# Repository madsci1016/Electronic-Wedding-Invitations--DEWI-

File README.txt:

/*
 * WeddingCard.c
 *
 * Created: 11/13/2012 8:11:05 PM
 *  Author: Bill&Mara
 *
 *	For project details see: http://www.billporter.info/?p=1655
 *
 *		 

*This program is free software: you can redistribute it and/or modify it under the terms of the GNU General Public License as published by the Free Software Foundation, either version 3 of the License, or(at your option) any later version.
This program is distributed in the hope that it will be useful,
but WITHOUT ANY WARRANTY; without even the implied warranty of
MERCHANTABILITY or FITNESS FOR A PARTICULAR PURPOSE.  See the
GNU General Public License for more details.
<http://www.gnu.org/licenses/>
*
*This work is licensed under the Creative Commons Attribution-ShareAlike 3.0 Unported License. 
*To view a copy of this license, visit http://creativecommons.org/licenses/by-sa/3.0/ or
*send a letter to Creative Commons, 444 Castro Street, Suite 900, Mountain View, California, 94041, USA.

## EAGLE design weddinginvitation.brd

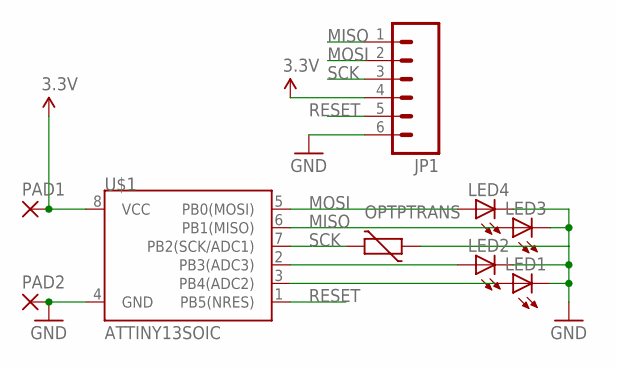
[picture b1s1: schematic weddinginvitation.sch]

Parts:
JP1: M06SMD-FEMALE-V2; 1X06-SMD-FEMALE-V2
LED1, LED2, LED3, LED4: LED1206; LED-1206
OPTPTRANS: VARISTORCN0805; CT/CN0805
PAD1, PAD2: SMD5; SMD2,54-5,08
U$1: ATTINY13SOIC; SO08

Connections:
3.3V: JP1.4, PAD1.1, U$1.8 (VCC)
GND: JP1.6, LED1.C, LED2.C, LED3.C, LED4.C, OPTPTRANS.1, PAD2.1, U$1.4 (GND)
MISO: JP1.1, LED3.A, U$1.6 (PB1(MISO))
MOSI: JP1.2, LED4.A, U$1.5 (PB0(MOSI))
unnamed: LED1.A, U$1.3 (PB4(ADC2))
unnamed: LED2.A, U$1.2 (PB3(ADC3))
RESET: JP1.5, U$1.1 (PB5(NRES))
SCK: JP1.3, OPTPTRANS.2, U$1.7 (PB2(SCK/ADC1))

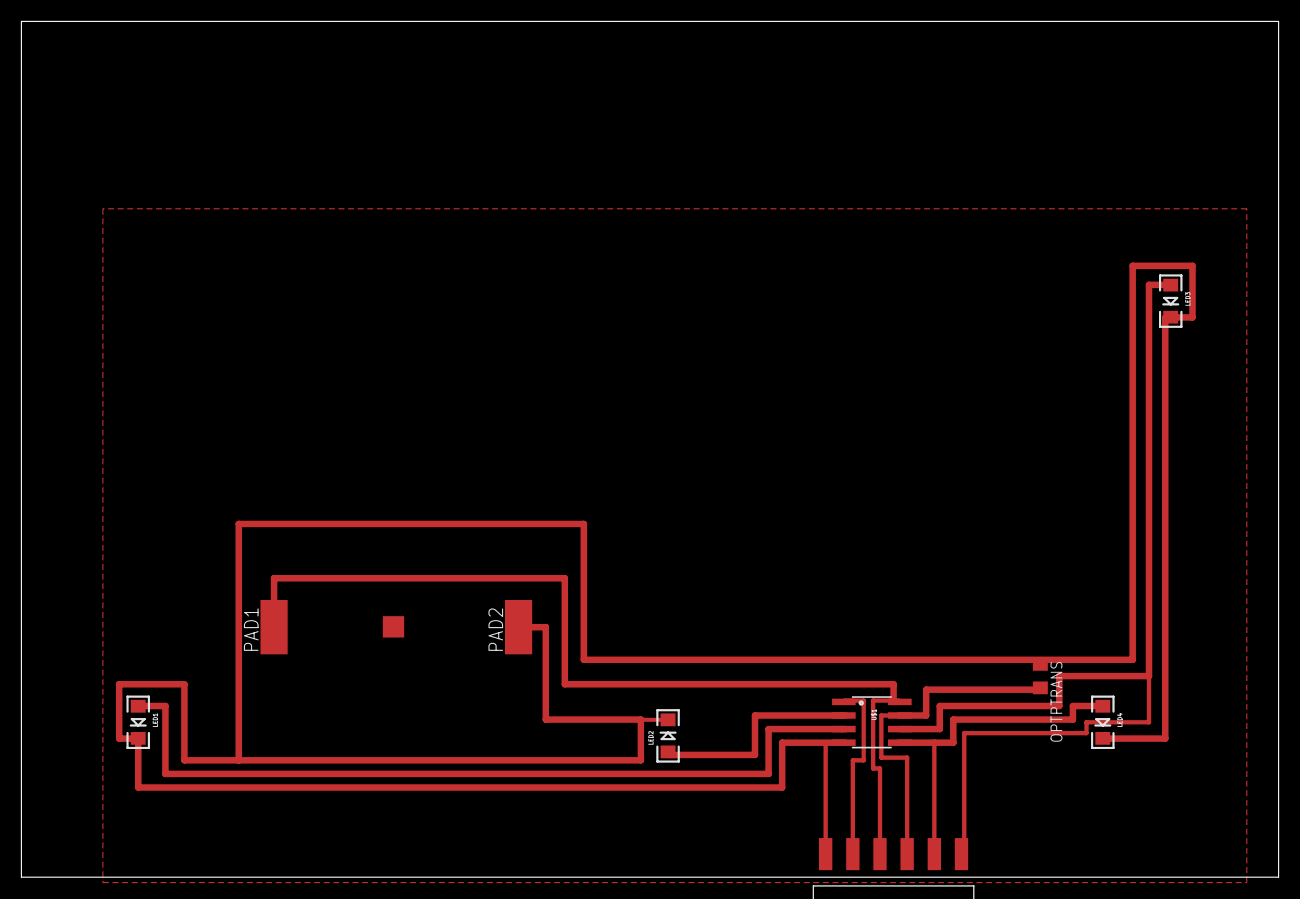
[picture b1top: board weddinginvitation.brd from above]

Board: 2 copper layers, 117.5 x 80.0 mm, 9 parts (0 on the bottom side), 8 nets.

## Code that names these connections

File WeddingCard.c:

/*
 * WeddingCard.c
 *
 * Created: 11/13/2012 8:11:05 PM
 *  Author: Bill&Mara
 *
 *	For project details see: http://www.billporter.info/?p=1655
 *
 *		Theory for sleep and light sensing inspired by:
 *			http://spritesmods.com/?art=minimalism&page=4	
 *				Though there were some bugs in the code and it didn't follow AVR Clib instructions
 *				for safe sleep; so I mostly rewrote the code to correct. 

 *
 */ 




#define F_CPU 1200000UL  // 1.2 MHz Though really it is less than this. timings will be off; not important

#include <util/delay.h>
#include <avr/io.h>
#include <avr/interrupt.h>
#include <avr/pgmspace.h>
#include <avr/sleep.h>
#include <avr/wdt.h>

//LED names match schematic. Backwards, I know. 
#define LED1 PB4 //ADC 2
#define LED2 PB3 //ADC 3
#define LED3 PB1 
#define LED4 PB0
#define SENSOR PB2 //ADC 1




//these ASM macros configure the WatchDog timer for interrupt only mode without touching the reset bit. 
//using the AVRClib macros (which touch the reset bit) was causing unexpected behavior. 
//pulled from http://www.avrfreaks.net/index.php?name=PNphpBB2&file=printview&t=51070&start=0
//It also means we don't need to keep touching the WDT interrupt bit.

#define wdt_set(value)   \
    __asm__ __volatile__ (  \
        "in __tmp_reg__,__SREG__" "\n\t"    \
        "cli" "\n\t"    \
        "wdr" "\n\t"    \
        "sts %0,%1" "\n\t"  \
        "out __SREG__,__tmp_reg__" "\n\t"   \
        "sts %0,%2" \
        : /* no outputs */  \
        : "M" (_SFR_MEM_ADDR(_WD_CONTROL_REG)), \
        "r" (_BV(_WD_CHANGE_BIT) | _BV(WDE)), \
            "r" ((uint8_t) ((value & 0x08 ? _WD_PS3_MASK : 0x00) | \
                _BV(WDTIE) | (value & 0x07)) ) \
        : "r0"  \
    ) 


#define wdt_off(x)   \
    __asm__ __volatile__ (  \
        "in __tmp_reg__,__SREG__" "\n\t"    \
        "cli" "\n\t"    \
        "wdr" "\n\t"    \
        "sts %0,%1" "\n\t"  \
        "sts %0,%2" \
        : /* no outputs */  \
        : "M" (_SFR_MEM_ADDR(_WD_CONTROL_REG)), \
        "r" (_BV(_WD_CHANGE_BIT) | _BV(WDE)), \
            "r" ((uint8_t) (0x00)) \
        : "r0"  \
    ) 

#define SETLOW(pin) (PORTB&=~(1<<pin))
#define ALLLEDS (1<<LED1)|(1<<LED2)|(1<<LED3)|(1<<LED4)

uint8_t incrementFrame(uint8_t);
void lightShow(void);
uint16_t getLight(void);
void easterEgg(void);
void powerOffUc(void);

//sparkle effect PWM values generated by Vixen Light Show software
static PROGMEM prog_uint8_t vixen_show_data[] = {0,0,0,178,163,148,133,118,103,88,73,58,43,0,0,0,0,0,178,163,148,178,178,163,148,133,118,178,163,178,163,148,133,118,103,178,178,163,148,133,118,178,163,148,178,178,163,148,133,178,163,148,133,118,178,163,148,178,163,178,178,163,148,133,178,178,163,148,178,163,148,133,178,163,148,133,178,178,163,148,133,178,163,148,178,163,178,163,148,133,118,103,178,163,148,178,178,163,148,178,163,148,133,118,103,178,163,148,178,178,163,148,133,118,103,88,73,58,43,178,163,148,133,118,103,88,73,58,43,0,0,0,0,0,0,0,0,0,0,0,0,0,178,163,178,163,148,133,178,178,163,148,133,118,103,88,178,163,148,133,118,103,178,163,148,133,118,103,88,73,58,43,0,0,178,163,178,163,148,133,118,103,88,73,58,178,163,148,133,118,103,88,73,58,43,0,178,127,76,0};

//easter egg storage
static PROGMEM prog_uint8_t easteregg[]={"-... .. .-.. .-.. / .- -. -.. / -- .- .-. .- / --. . . -.- ... / - --- --. . - .... . .-. / ..-. --- .-. . ...- . .-. .-.-.-"};
	
uint8_t frame1, frame2, frame3, frame4; //index for each LED channel
uint8_t match1, match2, match3, match4; //match compare for Software PWM
uint8_t triggercount;

uint16_t threshold;

int main(void)
{
	
	//set IO Direction
	DDRB = ALLLEDS;	
	
	//flash all LEDs on/off
	PORTB = ALLLEDS;
	_delay_ms(200);
	PORTB = 0;
	_delay_ms(1000);
	
	//From here on in the micro will always be powered. So we'll capture ambient light first and store it as the threshold. 
	//this means shorting reset will re-cal this threshold
	threshold = getLight();
	//egthreshold = getLight(ALED2);
	
	//flash all LEDs on/off
	PORTB = ALLLEDS;
	_delay_ms(200);
	PORTB = 0;
	//_delay_ms(1000);
	
	
	//lets go ahead and get ready for bed
	set_sleep_mode(SLEEP_MODE_PWR_DOWN);
	
	//main 'loop'
	while(1){
		//see if we should go to sleep or start the show
		if(getLight()<threshold) 						
			lightShow();
		else
			powerOffUc();
			

	}
	
    
}	

uint16_t getLight(void) {
    
	uint16_t val;
    
	
	//select correct ADC pin and voltage reference
	ADMUX=(1<<REFS0)|(1<<MUX0);
    ADCSRA=0x83;//enable adc, max prescaler
	
	//turn on pullup
	PORTB = (1<<SENSOR);
	
	//read ADC
    ADCSRA|=0x40; //go do adc
    while(ADCSRA&0x40) ; //wait till adc is done
    val=ADC;
	
	//disable adc
    ADCSRA=0; 
	
	//turn off pullup
    PORTB = 0;
	
    return val;
}


void lightShow(void){
	
	//make sure they are set to output
    DDRB = ALLLEDS;
	
	//load index starts
	frame1=0;
	frame2=50;
	frame3=100;
	frame4=150;
	
	for(uint8_t z=0; z<=200; z++)//run the show for 20 seconds. 
		{
			//Software PWM for the 4 channels. 
		
			//load match compares from program memory. Doing this once each time saves cycles.
			match1 = pgm_read_byte(&(vixen_show_data[frame1]));
			match2 = pgm_read_byte(&(vixen_show_data[frame2]));
			match3 = pgm_read_byte(&(vixen_show_data[frame3]));
			match4 = pgm_read_byte(&(vixen_show_data[frame4]));
		
			//freerun PWM for so many times and set pin low on compare
			for(uint8_t y=0; y<18; y++){ //each y is a PWM period. run so many PWM periods. See clock math below
				
				//set all pins HIGH
				PORTB = ALLLEDS;
				
				for(uint8_t i=0; i<255; i++){ //each i is a PWM division where compares should be made
					if(match1 == i) SETLOW(LED1); //each of these lines take 4 clocks 
					if(match2 == i) SETLOW(LED2);
					if(match3 == i) SETLOW(LED3);
					if(match4 == i) SETLOW(LED4); //so I used 16 clocks to compare all channels. 
					
					//16 clocks per PWM division x 255 divisions = 4080 clocks per PWM period
					//at 1.2Mhz that's a PWM freq of ~300 Hz. Good enough, no need to delay
					//Since Light show is 10Hz, each PWM period should be repeated 30 times. 
					// But with 3V the RC oscillator runs slower than predicted. Changed to 
					// 18 times through experimentation. 
				}
				
			
			}
		
		//move frame index's up
		frame1 = incrementFrame(frame1);
		frame2 = incrementFrame(frame2);
		frame3 = incrementFrame(frame3);
		frame4 = incrementFrame(frame4);
	}
	
		//after show, run easter egg if led is in dark
	if(getLight()>threshold) 
		easterEgg();
}

//quick function to move indexs up by one and wrap around
uint8_t incrementFrame(uint8_t framez) {
	
	framez++;
	if (framez > 199) framez = 0;
	
	return framez;
}

void easterEgg(){
	
	//make sure they are set to output
    //DDRB = 0b00011110;
	
	#define timeunit 180
	
	_delay_ms(timeunit*7);
	
	char temp = 0;
	
	for(int i=0; i<sizeof(easteregg); i++){
		
		temp = pgm_read_byte(&(easteregg[i]));
		
		if (temp == '.') {
			//set all pins HIGH
			PORTB = ALLLEDS;
			_delay_ms(timeunit);
			PORTB = 0;
			_delay_ms(timeunit);
		}
		else if (temp == '-') {
			//set all pins HIGH
			PORTB = ALLLEDS;
			_delay_ms(timeunit*3);
			PORTB = 0;
			_delay_ms(timeunit);
		}
		else if (temp == ' ') {
			//interletter delay, 3 dots
			_delay_ms(timeunit*3);
		}
		else //interword delay, 7 dots
			_delay_ms(timeunit*7);
		
	}
	
}

ISR(WDT_vect) {
		//empty interrupt routine 

}

//Configure the uC for power saving and enter sleep
//As written this function will return when the Watchdog alarm goes off.
//but won't reset the uC so RAM is safe. 
void powerOffUc(void) {
    
	//set IO for power save
	PORTB=0; DDRB=0;
	//get ready for bed
	sleep_enable();
	//need interrupts running for WDT alarm to work
	sei();
	//set wakeup for 2 seconds from now
	wdt_set(WDTO_2S);
	//go to sleep
	sleep_cpu();
	//wake up from sleep
	sleep_disable();  
	//turn off alarm
	wdt_off(); 
	//I don't use interrupts anyway. Leave em off. 
	cli();
}

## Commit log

2013-01-30 Added Eagle Files

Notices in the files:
parts and their libraries:
SparkFun: Licensing: CC v3.0 Share-Alike You are welcome to use this library for commercial purposes.
